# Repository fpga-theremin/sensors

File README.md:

# sensors
Implementation of Analog Front End for digital theremin sensor

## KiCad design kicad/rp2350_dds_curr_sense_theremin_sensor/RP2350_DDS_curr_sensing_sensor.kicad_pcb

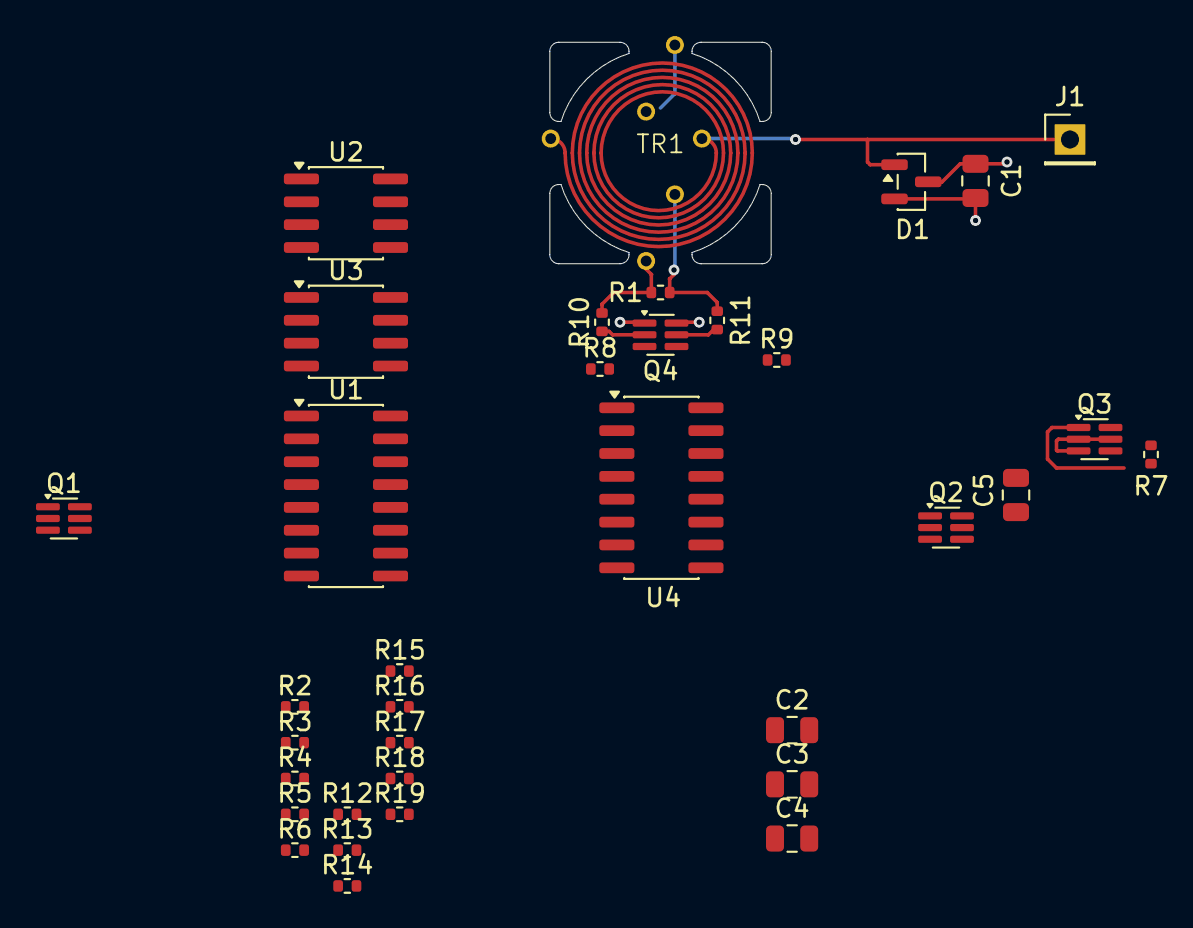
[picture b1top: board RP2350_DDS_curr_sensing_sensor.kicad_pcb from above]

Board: 4 copper layers, 35 parts (0 on the bottom side), 28 nets.

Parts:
C1, C2, C3, C5: 220n; C_0805_2012Metric
C4: 22n; C_0805_2012Metric
D1: CM1213A-01SO; SOT-23
J1: Conn_Inductor; PinHeader_1x01_P2.54mm_Vertical
Q1, Q2, Q3, Q4: BCM857BS; SOT-363_SC-70-6
R1, R3, R4, R5, R6: 100; R_0402_1005Metric
R2, R7, R12, R13: 4.7k; R_0402_1005Metric
R8, R9: 10; R_0402_1005Metric
R10, R11: 1; R_0402_1005Metric
R14, R15, R16: 10k; R_0402_1005Metric
R17, R18, R19: 200; R_0402_1005Metric
TR1: TRANSF3A; CurrSensTrans3
U1, U4: LM13700; SOIC-16_3.9x9.9mm_P1.27mm
U2: LMH6643MAX; SOIC-8_3.9x4.9mm_P1.27mm
U3: MCP6022T; SOIC-8_3.9x4.9mm_P1.27mm

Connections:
/Sensor_AFE/LC_DRV: D1.1 (CH1), J1.1, TR1.1
/Sensor_AFE/MBIASN: Q4.6 (C1), U4.1
/Sensor_AFE/MBIASP: Q4.3 (C2), U4.16
/Sensor_AFE/SBIAS: Q3.2 (B1), Q3.3 (C2), Q3.5 (B2), R7.2
/Sensor_AFE/SBN: Q4.2 (B1), R10.2
/Sensor_AFE/SBP: Q4.5 (B2), R11.2
/Sensor_AFE/SEN: Q4.1 (E1), R8.2
/Sensor_AFE/SENSEN: R1.1, R10.1, TR1.6
/Sensor_AFE/SENSEP: R1.2, R11.1, TR1.3
/Sensor_AFE/SEP: Q4.4 (E2), R9.1
/Sensor_AFE/VREF: TR1.4, TR1.5
GND: C1.2, C2.2, C3.2, C4.2, C5.2, D1.3 (VN), Q2.6 (C1), R2.1, R7.1, R17.2, R18.2, R19.2, U1.6 (V-), U4.6 (V-)
unnamed: C4.1, U4.5, U4.12
unnamed: Q1.2 (B1), Q1.3 (C2), Q1.5 (B2), R2.2
unnamed: Q1.6 (C1), R3.1, R4.2
unnamed: Q2.2 (B1), R6.2
unnamed: Q2.1 (E1), R4.1
unnamed: Q2.5 (B2), R5.1
unnamed: Q2.4 (E2), R3.2
unnamed: Q3.6 (C1), R8.1, R9.2
unnamed: R13.1, U1.15 (DIODE_BIAS)
unnamed: R12.1, U1.2 (DIODE_BIAS)
unnamed: R19.1, U4.14 (+)
unnamed: R16.1, R17.1, U4.3 (+), U4.13 (-)
unnamed: R15.1, U4.15 (DIODE_BIAS)
unnamed: R18.1, U4.4 (-)
unnamed: R14.1, U4.2 (DIODE_BIAS)
VDDA: C1.1, C2.1, C3.1, C5.1, D1.2 (VP), Q1.1 (E1), Q1.4 (E2), Q3.1 (E1), Q3.4 (E2), R12.2, R13.2, R14.2, R15.2, U1.11 (V+), U4.11 (V+)

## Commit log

2023-07-25 theremin AFE drive buffer with current sensing and LVDS outputs - LTSpice model
2023-07-31 current sensing oscillator - simple bjt OTA
2023-07-31 minor fixes in single OTA oscillator
2023-07-31 add ltspice simulation of OTA current sensing oscillator with automatic gain control
2023-07-31 add ltspice simulation images
2023-07-31 add images for ltspice simulation, update readme
2023-07-31 simplified oscillator model - 8BJTs
2023-08-03 current sensing oscillator
2023-08-08 current sensing oscillator model, v10
2023-08-08 update readme with new oscillator v10
2023-08-17 osciilator v12 spice model
2023-08-17 update readme with new spice model
2023-12-04 FPGA sensor module readme
2023-12-06 fpga sensor simulator Qt app
2023-12-06 sensor sim app improvements
2023-12-08 fixes in sim
2023-12-08 sim app improvements
2023-12-11 update theory docs
2023-12-19 sensor simulator improved
2023-12-20 simulator update; spreadsheet with some simulation results
2023-12-21 update simulator code - sine table
2024-01-02 simulator improvements
2024-01-02 sallen key shielded afe simulation
2024-01-02 sallen-key model
2024-01-02 update spice simulation
2024-01-03 sallen key shielded sensor model
2024-01-03 update sallen-key models
2024-01-03 update FPGA sensor readme
2024-01-04 block diagram
2024-01-04 update simulator - add ADC interpolation; update readmes
2024-01-04 update readmes, 12bit 40MHz ADC selected
2024-01-04 initial version of verilog code
2024-01-05 update verilog - high frequency frontend part, update simulator - extended settings range
2024-01-05 fix error in verilog code
2024-01-05 verilog update; add RF part diagram
2024-01-06 update diagram with phase increment feedback
2024-01-06 verilog testbench
2024-01-06 fpga verilog - fix lp filter
2024-01-06 lp filters
2024-01-06 op filters fixed
2024-01-06 verilog: fix quadrature mul_and_accumulate module, add testbench
2024-01-07 FPGA RF SDR part - testbench passed
2024-01-07 improve LP filter
2024-01-08 lp filter improvements: support out_data_bits > in_data_bits
2024-01-08 hardware simulation classes
2024-01-08 FPGA firmware: add signed LP filter:
2024-01-08 fixes of filter parameters
2024-01-08 filter parameter fixes
2024-01-08 firmware fixes: mem init file, lp filter fixes
2024-01-09 add icecube2 project
2024-01-09 FPGA firmware - advanced low resources filters
2024-01-10 fpga hdl - filter control
2024-01-10 verilog: filter for quadrature mul acc
2024-01-11 sim ui improvement
2024-01-11 simulator: simulation batch dialog - in progress
2024-01-13 sensor PLL diagram
2024-01-13 simulator: simulation batch in separate thread
2024-01-13 simulator - sim suite fixes
2024-01-15 simulator parameter types refactoring
2024-01-15 sim params refactoring
2024-01-15 simulator: stats plot fixes
2024-01-15 simulator: precision stats plot improvements
2024-01-15 simulator: stats charts improvements
2024-01-16 simulator fixes
2024-01-16 simulator - improve bit stats charts
2024-01-16 simulator: add LP filter
2024-01-16 simulator: filters on/off
2024-01-21 phase detection research readme
2024-01-21 phase detection research
2024-01-21 research
2024-01-21 simulator update - cordic sin_cos
2024-01-22 phase detection research, additional findings
2024-01-22 phase detection research - excel simulation, circle center position calculation added
2024-01-23 phase shift calculation alternative method - how it's affected by DC offset in ADC signal
2024-01-31 simulator - new phase shift detector - 4points
2024-02-01 simulator - new filtering
2024-02-02 CORDIC simulation
2024-02-02 cordic fixes
2024-02-06 CORDIC sinCos
2024-02-06 CORDIC sin cos - verilog implementation
2024-02-07 CORDIC sin cos implementation FPGA verilog
2024-02-08 CORDIC SIN COS verilog passes tests
2024-02-08 fixes in CORDIC sin cos verilog impl
2024-02-08 CORDIC sin cos
2024-02-09 CORDIC
2024-08-01 current sensor oscillator LTSpice model:
2024-08-06 fix schematic of sensor
2024-08-06 current sensing buffer
2024-08-09 gain control for current sensing buffer - ltspice model
2024-08-09 D-Lev AFE replacement model
2024-11-29 D-lev AFE with current sensing - spice model
2024-12-02 add simplified schematic, w/o LP filter buffer
2024-12-03 D-Lev AFE model with integrating current sensor
2024-12-05 improve afe - remove comparator
2025-02-03 vco model
2025-03-26 VCO and drive LTSpice model on BJT
2025-03-26 add readme and images
2025-03-28 theremin sensor oscillator with PLL - LTSpice model
2025-03-31 simplified version of PLL
2025-03-31 pll oscillator v4 - opamp as output buffer
2025-04-01 current sensing oscillator model
2025-04-02 simple current sensing DLev AFE
2025-04-02 current sensing dlev afe v2
2025-04-02 4046 pll osc, part 1
2025-04-02 update PLL model
2025-04-05 dlev afe
2025-07-19 simple current sensing oscillator model : current mirrors + unbuffered inverters
2025-09-23 planar PCB spiral transformer generator
2025-09-23 transformer footprint generator
2025-09-23 sample footprint
2025-12-31 SVF VCO PLL theremin oscillator
2025-12-31 add insubmitted models
2026-01-09 LM13700 based VCO
2026-01-09 fix readme
2026-01-09 Theremin Sensor - PLL on LM13700
2026-03-02 VCO simple bjt+opamp SVF
2026-03-03 update VCO bjt+opamp SVF model
2026-03-13 commit recent changes for ltspice models experiments
2026-03-16 analog PLL model
2026-03-16 analog PLL oscillator - working good
2026-03-17 pll oscillator, good|
2026-03-17 new analog PLL theremin oscillator
2026-03-23 PCB Transformer generator, 1:2
2026-03-26 DAC sim pwl generator
2026-03-31 add rp2350 sensor kicad project, initial version
